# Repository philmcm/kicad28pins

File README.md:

Adaptation of 28-PINS PROJECT by FEDEVEL ACADEMY to KiCad
http://www.28pins.com

Adaptation by Phil McMillan, September 2018

(c) 2015 Designed by FEDEVEL Academy http://www.fedevel.com/academy. Based on Arduino: http://www.arduino.cc. Released under Creative Commons Attribution-ShareAlike 3.0 Unported.

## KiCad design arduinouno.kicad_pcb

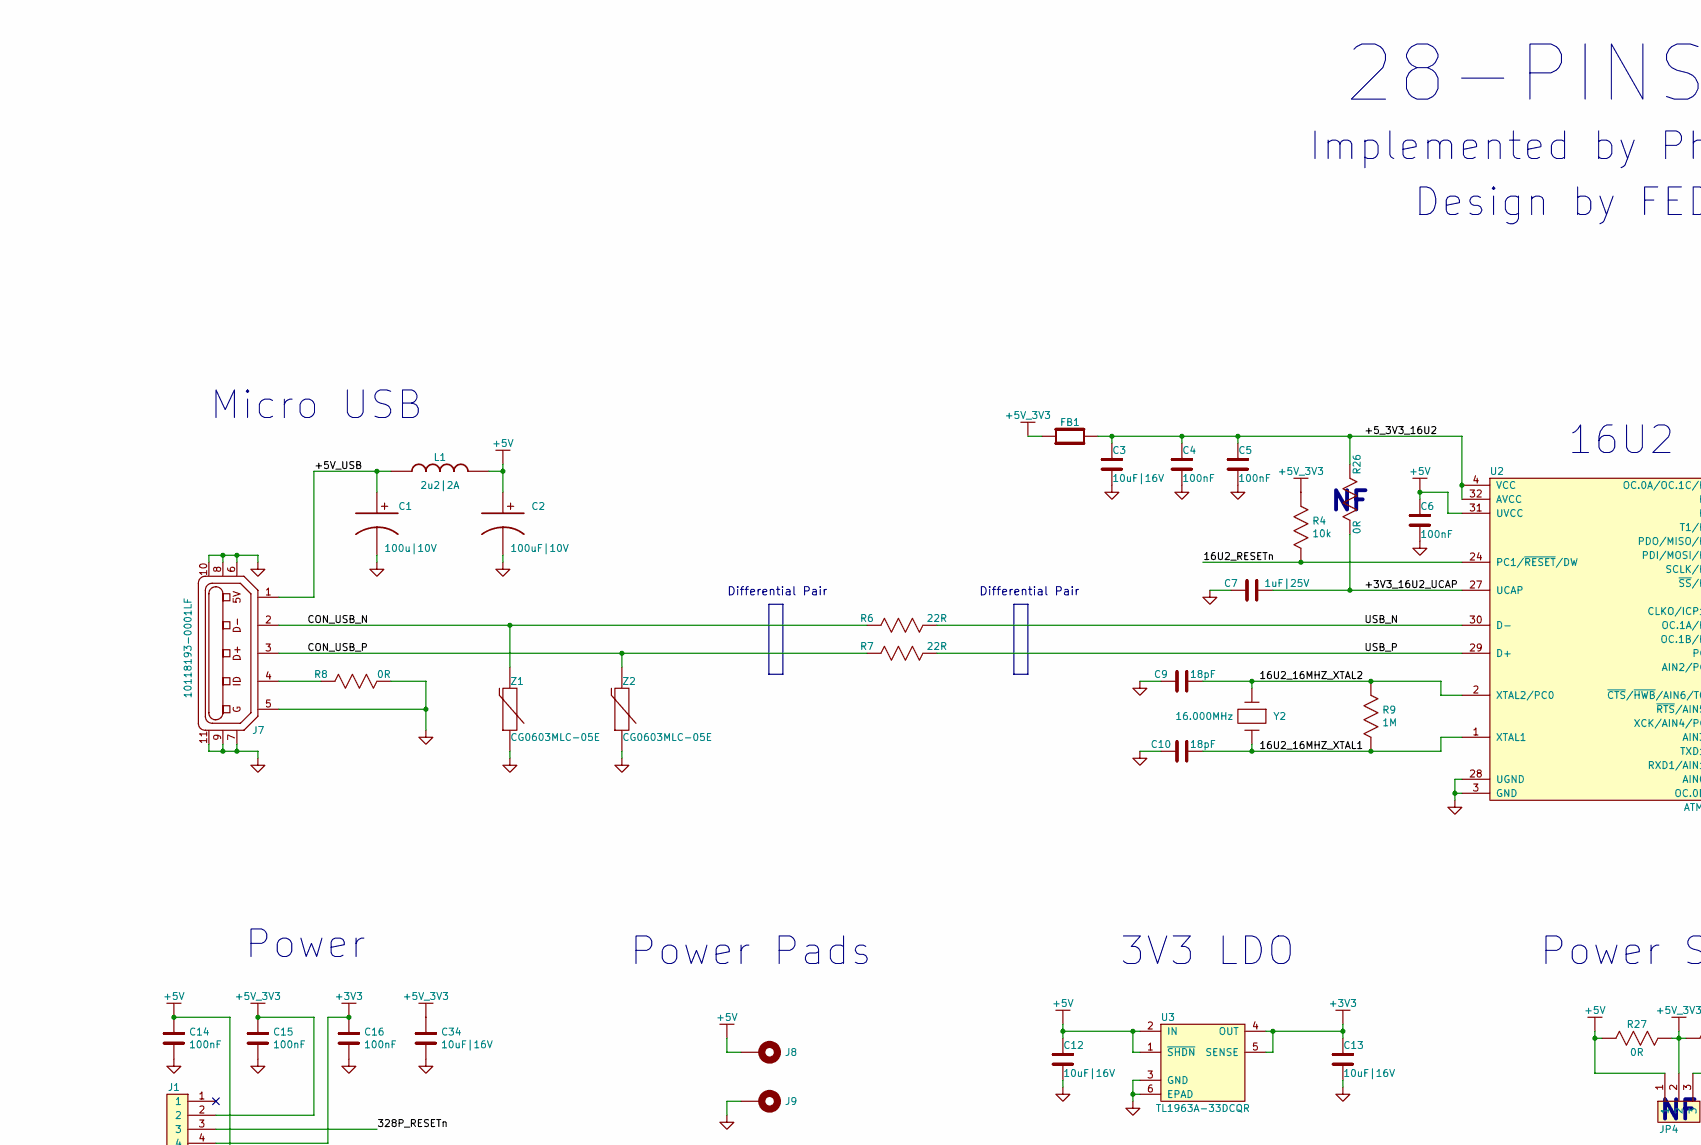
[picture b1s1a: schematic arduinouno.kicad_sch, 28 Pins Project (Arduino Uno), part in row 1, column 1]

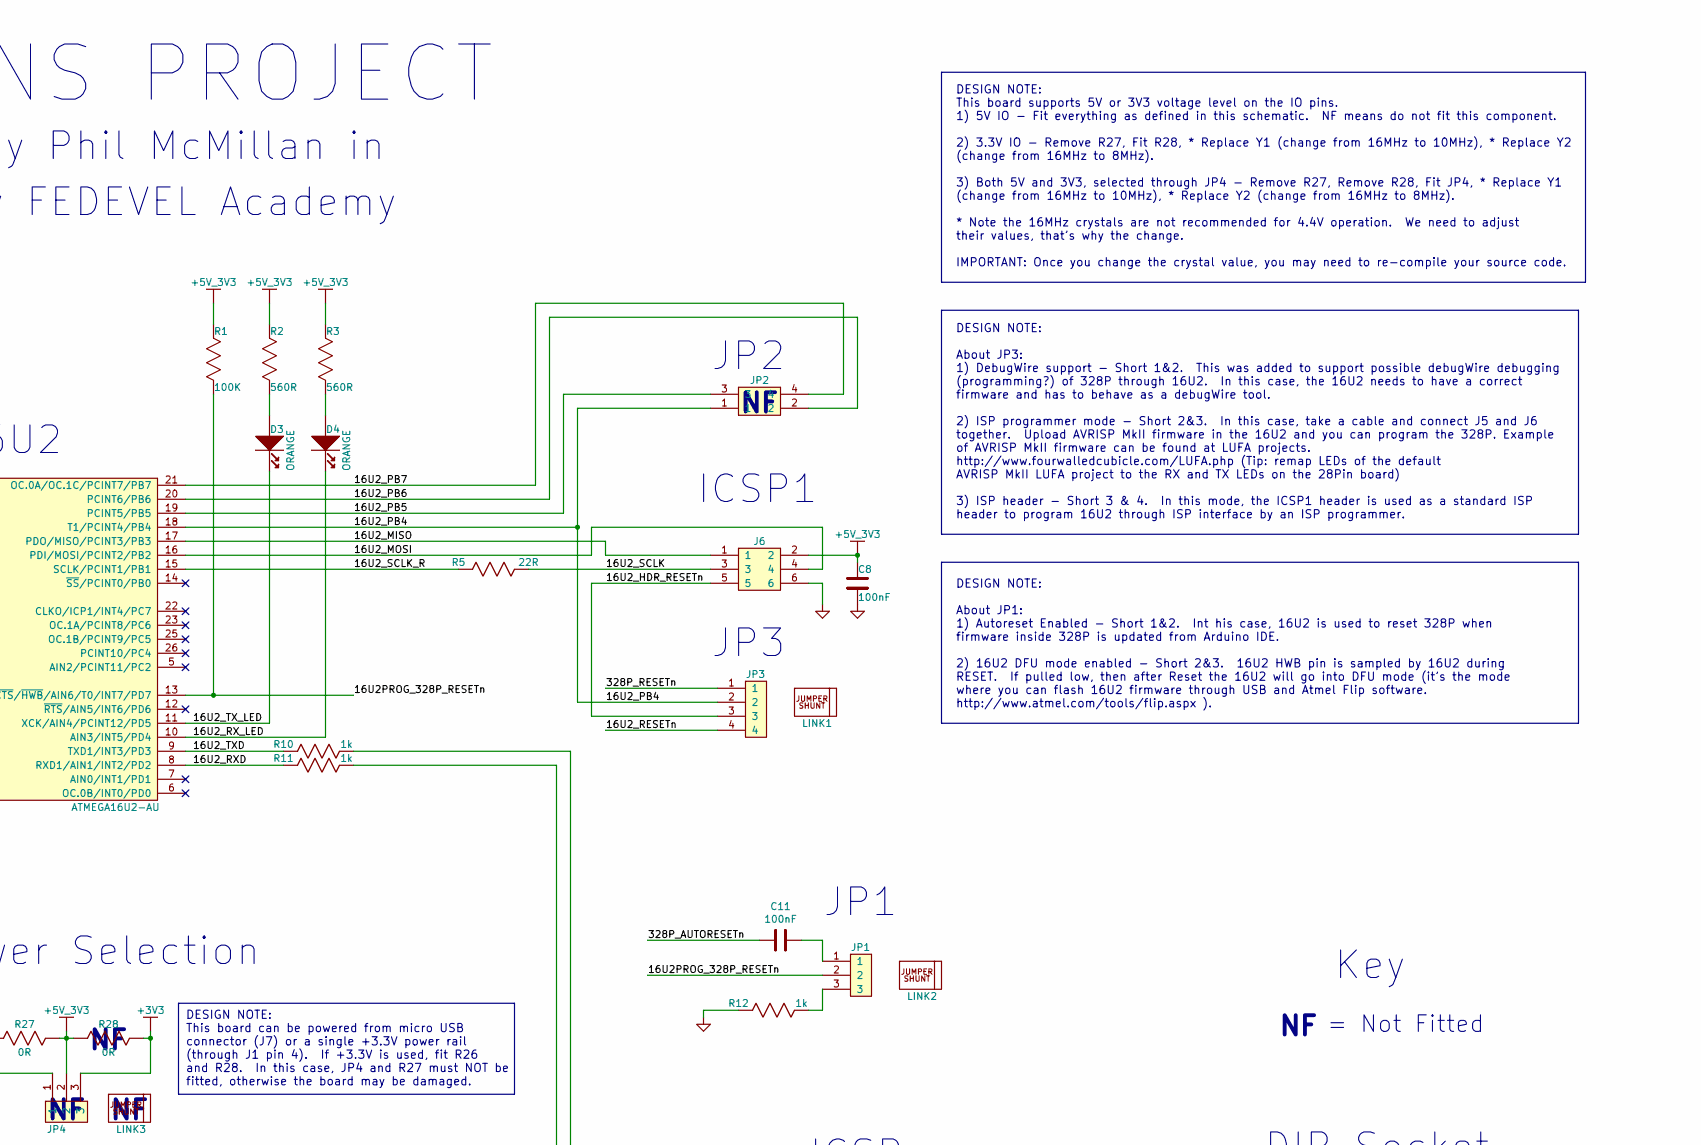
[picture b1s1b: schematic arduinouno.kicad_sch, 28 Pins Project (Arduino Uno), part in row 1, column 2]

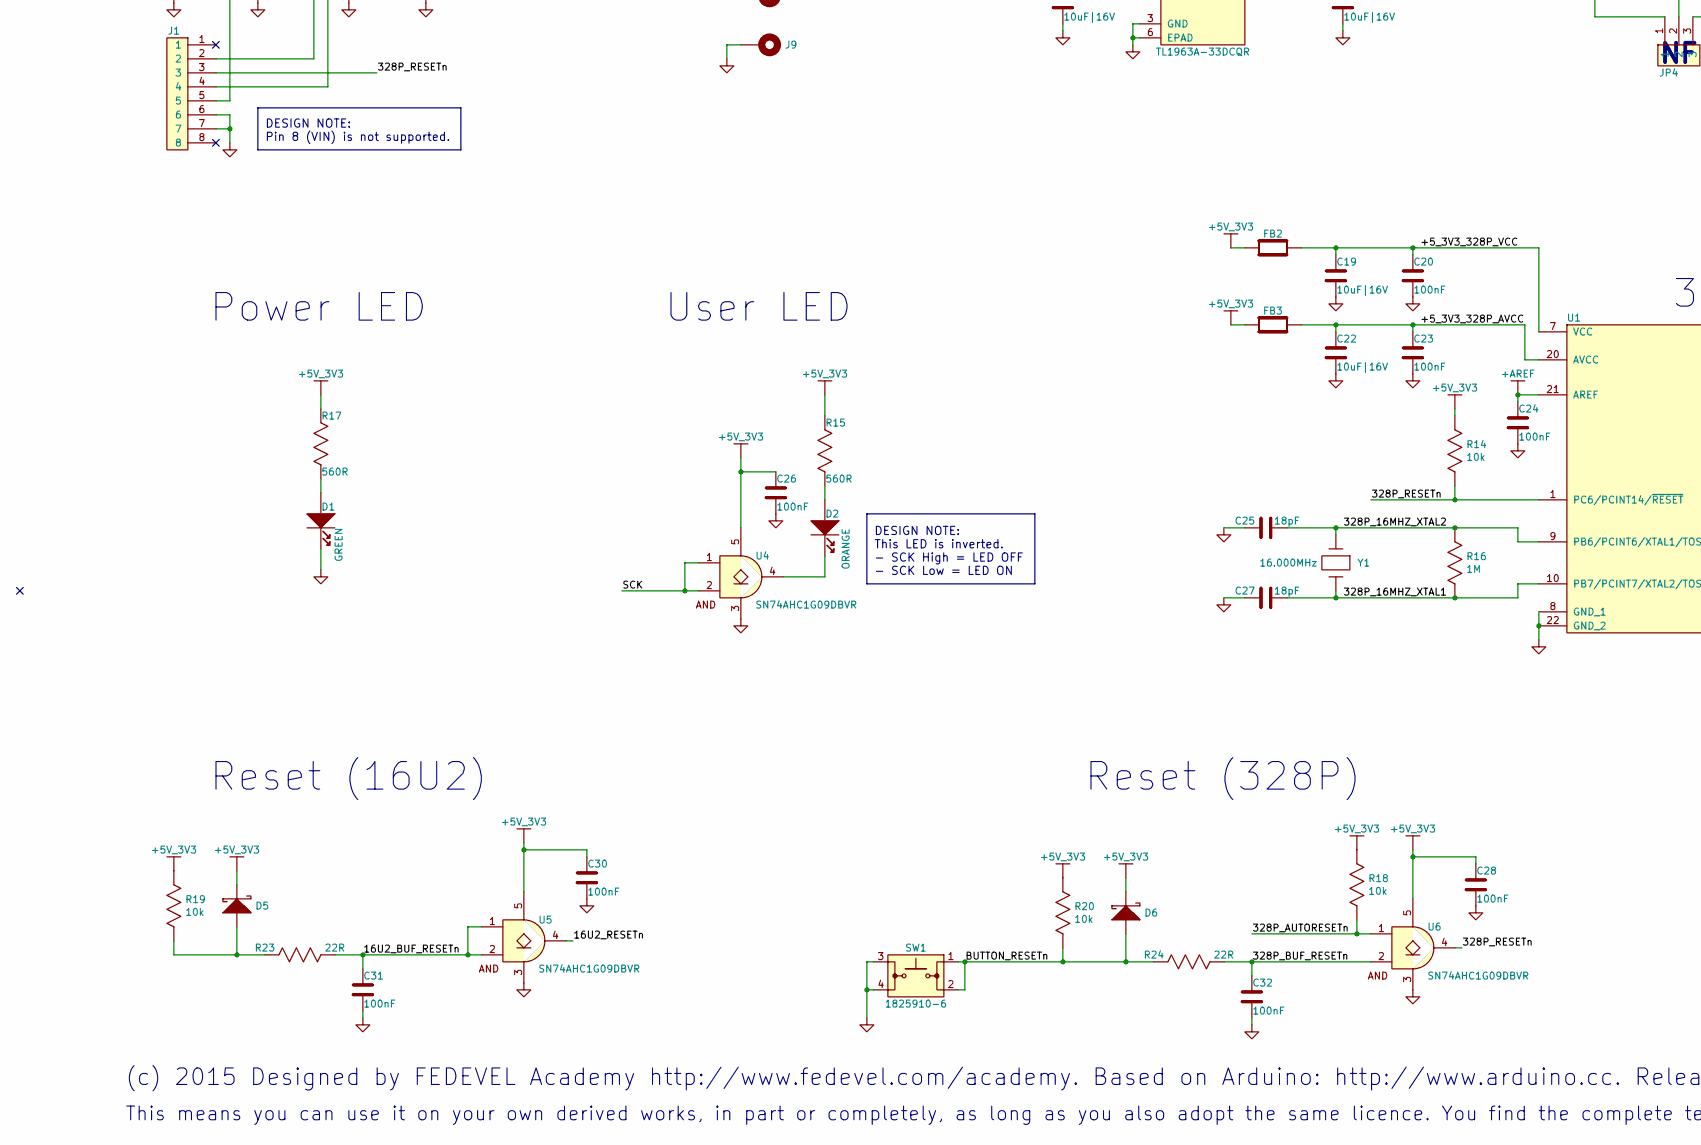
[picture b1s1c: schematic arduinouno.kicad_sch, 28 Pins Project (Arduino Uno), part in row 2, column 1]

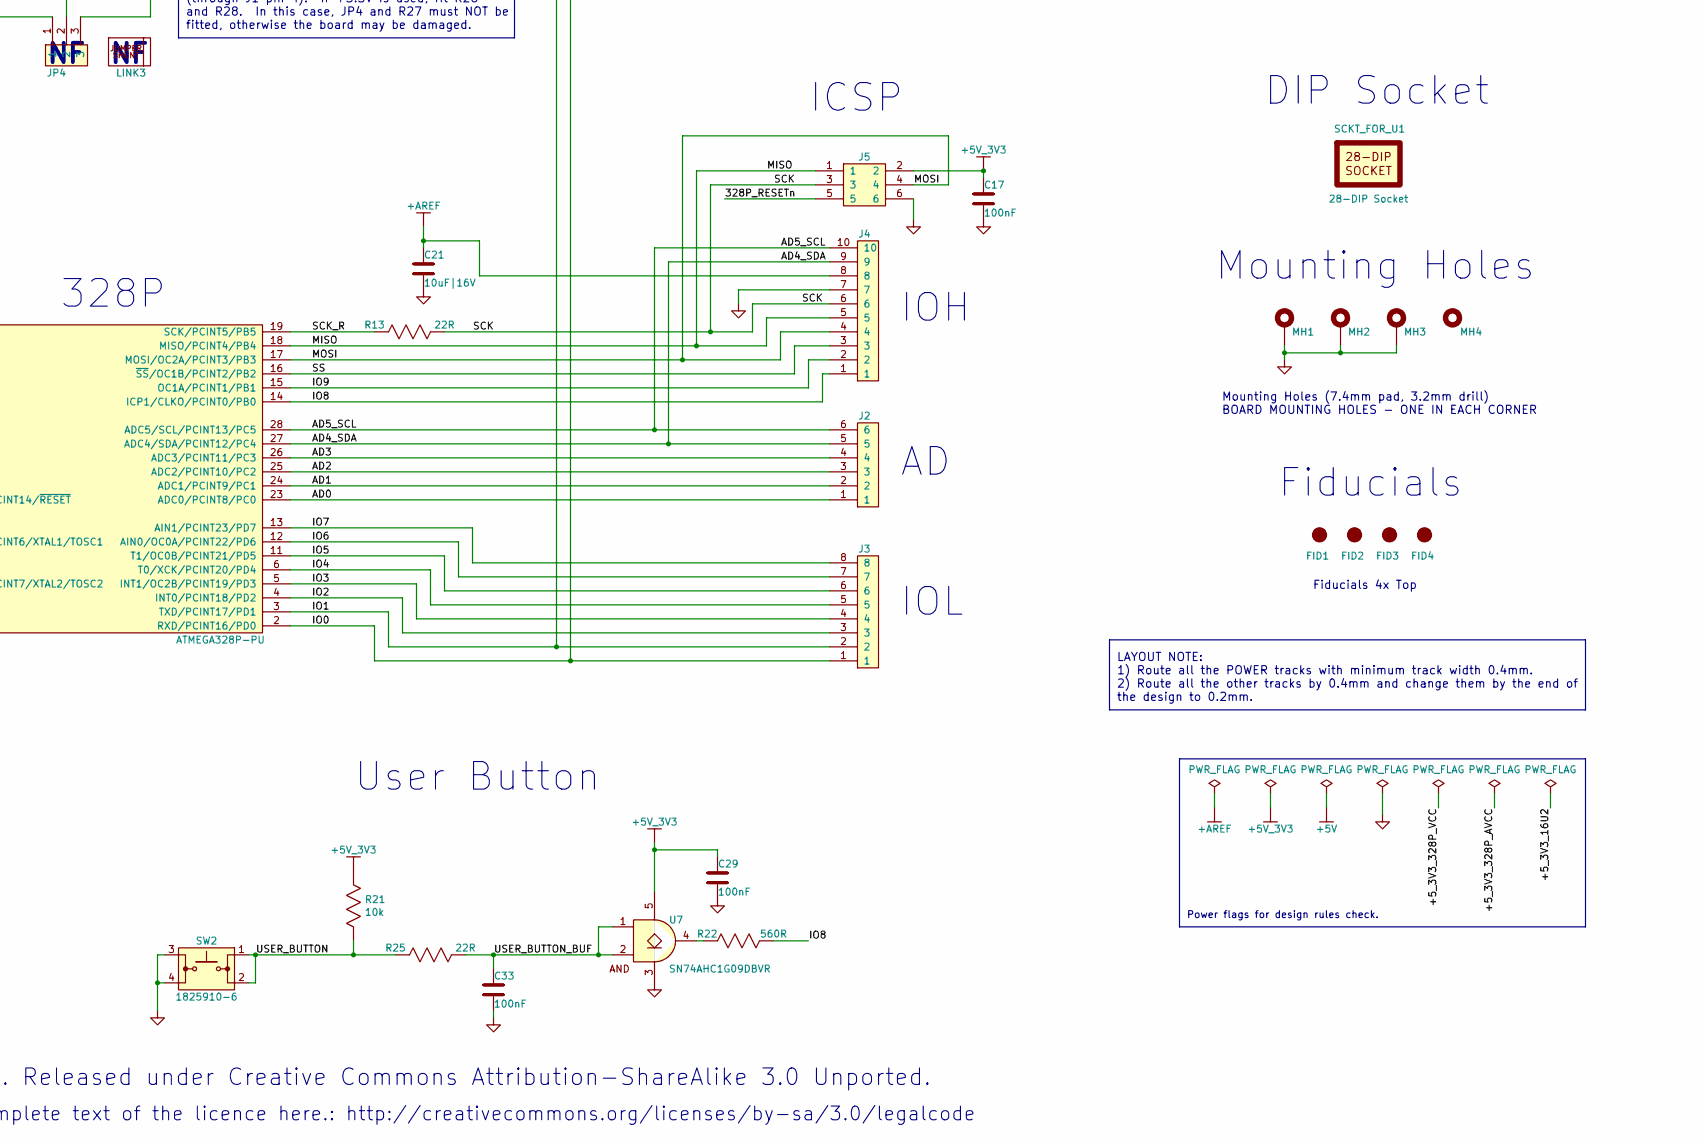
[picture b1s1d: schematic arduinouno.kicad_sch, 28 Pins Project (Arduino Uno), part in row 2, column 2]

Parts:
C1: 100u|10V; C_ALUM_C_SIZE; Digikey PCE3867TR-ND
C2: 100uF|10V; C_ALUM_C_SIZE; Digikey PCE3867TR-ND
C3, C12, C13, C19, C21, C22, C34: 10uF|16V; C0805x145mm; Digikey 445-7645-1-ND
C4, C5, C6, C8, C11, C14, C15, C16, C17, C20, C23, C24, C26, C28, C29, C30, C31, C32, C33: 100nF; C0805x95mm; Digikey 445-7534-1-ND
C7: 1uF|25V; C0805x95mm; Digikey 445-1419-1-ND
C9, C10, C25, C27: 18pF; C0805x95mm; Digikey 399-8029-1-ND
D1: GREEN; LED_0603; Digikey 475-2709-1-ND
D2, D3, D4: ORANGE; LED_0603; Digikey 475-2740-1-ND
D5, D6: BAT54HT1G; SOD323; Digikey BAT54HT1GOSTR-ND
FB1, FB2, FB3: MPZ2012S601AT000; FB0805x85mm; Digikey 445-7645-1-ND
FID1, FID2, FID3, FID4: FID_1MM; FID_40x120M
J1, J3: M20-7820842; 8P_Header_Female_2.54mm; Digikey 952-1823-ND
J2: M20-7820646; 6P_Header_Female_2.54mm; Digikey 952-1809-ND
J4: M20-7821046; 10P_Header_Female_2.54mm; Digikey 952-1847-ND
J5, J6: 67997-106HLF; HDR_2x3_2.54mm; Digikey 609-3393-ND
J7: 10118193-0001LF; 10118193; Digikey 609-4616-1-ND
J8, J9: PAD_WITH_HOLE_4mmx1.5mm
JP1, JP4: 68000-103HLF; 3P_Header_2.54mm; Digikey 609-3461-ND
JP2: 68602-104HLF; HDR_2x2_2.54mm; Digikey 609-3361-ND
JP3: 68001-204HLF; 4P_Header_2.54mm; Digikey 609-3402-ND
L1: 2u2|2A; C1210_INDUCTOR; Digikey 399-9598-1-ND
LINK1, LINK2, LINK3: QPC02SXGN-RC; Digikey S9337-ND
MH1, MH2, MH3: MH_7.4MMCx3.2MMD
MH4: MH_7.4MMNCx3.2MMD; MH_7.4MMCx3.2MMD_NON_COPPER_NPTH
R1: 100K; R0805x60mm; Digikey 311-100KCRCT-ND
R2, R3, R15, R17, R22: 560R; R0805x60mm; Digikey 311-560CRCT-ND
R4, R14, R18, R19, R20, R21: 10k; R0805x60mm; Digikey 311-10.0KCRCT-ND
R5, R6, R7, R13, R23, R24, R25: 22R; R0805x60mm; Digikey 311-22.0CRCT-ND
R8, R26, R27, R28: 0R; R0805x60mm; Digikey 311-0.0ARCT-ND
R9, R16: 1M; R0805x60mm; Digikey 311-1.00MCRCT-ND
R10, R11, R12: 1k; R0805x60mm; Digikey 311-1.00KCRCT-ND
SCKT_FOR_U1: 28-DIP Socket; 28DIP_7.62MM_SCKT; Digikey 3M5480-ND
SW1, SW2: 1825910-6; Digikey 450-1650-ND
U1: ATMEGA328P-PU; 28PIN_PDIP_7.62mm; Digikey ATMEGA328P-PU-ND
U2: ATMEGA16U2-AU; QFP-32_8.4x8.4_Pitch0.8mm; Digikey ATMEGA16U2-AU-ND
U3: TL1963A-33DCQR; DCQ_R-PDSO-G6; Digikey 296-24534-1-ND
U4, U5, U6, U7: SN74AHC1G09DBVR; DBV_SOT23_5; Digikey 296-29202-1-ND
Y1, Y2: 16.000MHz; ABM7_BIG; Digikey 535-9840-1-ND
Z1, Z2: CG0603MLC-05E; R_0603; Digikey CG0603MLC-05ECT-ND

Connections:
+3V3: C13.1, C16.1, J1.4, JP4.3, R28.2, U3.4 (OUT), U3.5 (SENSE)
+5V: C2.1, C6.1, C12.1, C14.1, J1.5, J8.1, JP4.1, L1.2, R27.1, U2.31 (UVCC), U3.1 (~SHDN), U3.2 (IN)
+5V_3V3: C8.1, C15.1, C17.1, C26.1, C28.1, C29.1, C30.1, C34.1, D5.1 (Cathode), D6.1 (Cathode), FB1.1, FB2.1, FB3.1, J1.2, J5.2, J6.2, JP4.2, R1.1, R2.1, R3.1, R4.1, R14.1, R15.1, R17.1, R18.1, R19.1, R20.1, R21.1, R27.2, R28.1, U4.5 (VCC), U5.5 (VCC), U6.5 (VCC), U7.5 (VCC)
+AREF: C21.1, C24.1, J4.8, U1.21 (AREF)
/16U2PROG_328P_RESETn: JP1.2, R1.2, U2.13 (~CTS/~HWB/AIN6/T0/INT7/PD7)
/16U2_16MHZ_XTAL1: C10.2, R9.2, U2.1 (XTAL1), Y2.2
/16U2_16MHZ_XTAL2: C9.2, R9.1, U2.2 (XTAL2/PC0), Y2.1
/16U2_BUF_RESETn: C31.1, R23.2, U5.1 (A), U5.2 (B)
/16U2_HDR_RESETn: J6.5, JP3.3
/16U2_MISO: J6.1, U2.17 (PDO/MISO/PCINT3/PB3)
/16U2_MOSI: J6.4, U2.16 (PDI/MOSI/PCINT2/PB2)
/16U2_PB4: JP2.1, JP3.2, U2.18 (T1/PCINT4/PB4)
/16U2_PB5: JP2.3, U2.19 (PCINT5/PB5)
/16U2_PB6: JP2.2, U2.20 (PCINT6/PB6)
/16U2_PB7: JP2.4, U2.21 (OC.0A/OC.1C/PCINT7/PB7)
/16U2_RESETn: JP3.4, R4.2, U2.24 (PC1/~RESET/DW), U5.4 (Y)
/16U2_RXD: R11.1, U2.8 (RXD1/AIN1/INT2/PD2)
/16U2_RX_LED: D4.1 (Cathode), U2.10 (AIN3/INT5/PD4)
/16U2_SCLK: J6.3, R5.2
/16U2_SCLK_R: R5.1, U2.15 (SCLK/PCINT1/PB1)
/16U2_TXD: R10.1, U2.9 (TXD1/INT3/PD3)
/16U2_TX_LED: D3.1 (Cathode), U2.11 (XCK/AIN4/PCINT12/PD5)
/328P_16MHZ_XTAL1: C27.2, R16.2, U1.10 (PB7/PCINT7/XTAL2/TOSC2), Y1.2
/328P_16MHZ_XTAL2: C25.2, R16.1, U1.9 (PB6/PCINT6/XTAL1/TOSC1), Y1.1
/328P_AUTORESETn: C11.1, R18.2, U6.1 (A)
/328P_BUF_RESETn: C32.1, R24.2, U6.2 (B)
/328P_RESETn: J1.3, J5.5, JP3.1, R14.2, U1.1 (PC6/PCINT14/~RESET), U6.4 (Y)
/+3V3_16U2_UCAP: C7.2, R26.2, U2.27 (UCAP)
/+5V_USB: C1.1, J7.1, L1.1
/+5_3V3_16U2: C3.1, C4.1, C5.1, FB1.2, R26.1, U2.4 (VCC), U2.32 (AVCC)
/+5_3V3_328P_AVCC: C22.1, C23.1, FB3.2, U1.20 (AVCC)
/+5_3V3_328P_VCC: C19.1, C20.1, FB2.2, U1.7 (VCC)
/AD0: J2.1, U1.23 (ADC0/PCINT8/PC0)
/AD1: J2.2, U1.24 (ADC1/PCINT9/PC1)
/AD2: J2.3, U1.25 (ADC2/PCINT10/PC2)
/AD3: J2.4, U1.26 (ADC3/PCINT11/PC3)
/AD4_SDA: J2.5, J4.9, U1.27 (ADC4/SDA/PCINT12/PC4)
/AD5_SCL: J2.6, J4.10, U1.28 (ADC5/SCL/PCINT13/PC5)
/BUTTON_RESETn: D6.2 (Anode), R20.2, R24.1, SW1.1, SW1.2
/CON_USB_N: J7.2, R6.1, Z1.2
/CON_USB_P: J7.3, R7.1, Z2.2
/IO0: J3.1, R10.2, U1.2 (RXD/PCINT16/PD0)
/IO1: J3.2, R11.2, U1.3 (TXD/PCINT17/PD1)
/IO2: J3.3, U1.4 (INT0/PCINT18/PD2)
/IO3: J3.4, U1.5 (INT1/OC2B/PCINT19/PD3)
/IO4: J3.5, U1.6 (T0/XCK/PCINT20/PD4)
/IO5: J3.6, U1.11 (T1/OC0B/PCINT21/PD5)
/IO6: J3.7, U1.12 (AIN0/OC0A/PCINT22/PD6)
/IO7: J3.8, U1.13 (AIN1/PCINT23/PD7)
/IO8: J4.1, R22.2, U1.14 (ICP1/CLKO/PCINT0/PB0)
/IO9: J4.2, U1.15 (OC1A/PCINT1/PB1)
/MISO: J4.5, J5.1, U1.18 (MISO/PCINT4/PB4)
/MOSI: J4.4, J5.4, U1.17 (MOSI/OC2A/PCINT3/PB3)
/SCK: J4.6, J5.3, R13.2, U4.1 (A), U4.2 (B)
/SCK_R: R13.1, U1.19 (SCK/PCINT5/PB5)
/SS: J4.3, U1.16 (~SS/OC1B/PCINT2/PB2)
/USB_N: R6.2, U2.30 (D-)
/USB_P: R7.2, U2.29 (D+)
/USER_BUTTON: R21.2, R25.1, SW2.1, SW2.2
/USER_BUTTON_BUF: C33.1, R25.2, U7.1 (A), U7.2 (B)
GND: C1.2, C2.2, C3.2, C4.2, C5.2, C6.2, C7.1, C8.2, C9.1, C10.1, C12.2, C13.2, C14.2, C15.2, C16.2, C17.2, C19.2, C20.2, C21.2, C22.2, C23.2, C24.2, C25.1, C26.2, C27.1, C28.2, C29.2, C30.2, C31.2, C32.2, C33.2, C34.2, D1.1 (Cathode), J1.6, J1.7, J4.7, J5.6, J6.6, J7.5, J7.6, J7.7, J7.8, J7.9, J7.10, J7.11, J9.1, MH1.1, MH2.1, MH3.1, R8.2, R12.1, SW1.3, SW1.4, SW2.3, SW2.4, U1.8 (GND_1), U1.22 (GND_2), U2.3 (GND), U2.28 (UGND), U3.3 (GND), U3.6 (EPAD), U4.3 (GND), U5.3 (GND), U6.3 (GND), U7.3 (GND), Z1.1, Z2.1
unnamed: C11.2, JP1.1
unnamed: D1.2 (Anode), R17.2
unnamed: D2.1 (Cathode), U4.4 (Y)
unnamed: D2.2 (Anode), R15.2
unnamed: D3.2 (Anode), R2.2
unnamed: D4.2 (Anode), R3.2
unnamed: D5.2 (Anode), R19.2, R23.1
unnamed: J7.4, R8.1
unnamed: JP1.3, R12.2
unnamed: R22.1, U7.4 (Y)

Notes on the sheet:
Reset (328P)
This means you can use it on your own derived works, in part or completely, as long as you also adopt the same licence. You find the complete text of the licence here.: http://creativecommons.org/licenses/by-sa/3.0/legalcode
Power Pads
Fiducials
Key
Power Selection
16U2
(c) 2015 Designed by FEDEVEL Academy http://www.fedevel.com/academy. Based on Arduino: http://www.arduino.cc. Released under Creative Commons Attribution-ShareAlike 3.0 Unported.
28-PINS PROJECT
IOH
Implemented by Phil McMillan in
User Button
DESIGN NOTE: This board supports 5V or 3V3 voltage level on the IO pins. 1) 5V IO - Fit everything as defined in this schematic. NF means do not fit this component. 2) 3.3V IO - Remove R27, Fit R28, * Replace Y1 (change from 16MHz to 10MHz), * Replace Y2 (change from 16MHz to 8MHz). 3) Both 5V and 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
Mounting Holes
Power LED
ICSP
Reset (16U2)
DESIGN NOTE: This LED is inverted. - SCK High = LED OFF - SCK Low = LED ON
Differential Pair
IOL
Design by FEDEVEL Academy
ICSP1
Power flags for design rules check.
328P
JP3
DESIGN NOTE: About JP1: 1) Autoreset Enabled - Short 1&2. Int his case, 16U2 is used to reset 328P when firmware inside 328P is updated from Arduino IDE. 2) 16U2 DFU mode enabled - Short 2&3. 16U2 HWB pin is sampled by 16U2 during RESET. If pulled low, then after Reset the 16U2 will go into DFU mod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
DESIGN NOTE: This board can be powered from micro USB connector (J7) or a single +3.3V power rail (through J1 pin 4). If +3.3V is used, fit R26 and R28. In this case, JP4 and R27 must NOT be fitted, otherwise the board may be damaged.
DIP Socket
User LED
DESIGN NOTE: Pin 8 (VIN) is not supported.
Mounting Holes (7.4mm pad, 3.2mm drill) BOARD MOUNTING HOLES - ONE IN EACH CORNER
LAYOUT NOTE: 1) Route all the POWER tracks with minimum track width 0.4mm. 2) Route all the other tracks by 0.4mm and change them by the end of the design to 0.2mm.
Fiducials 4x Top
DESIGN NOTE: About JP3: 1) DebugWire support - Short 1&2. This was added to support possible debugWire debugging (programming?) of 328P through 16U2. In this case, the 16U2 needs to have a correct firmware and has to behave as a debugWire tool. 2) ISP programmer mode - Short 2&3. In this case, take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
JP1
Power
3V3 LDO
JP2
= Not Fitted
Micro USB

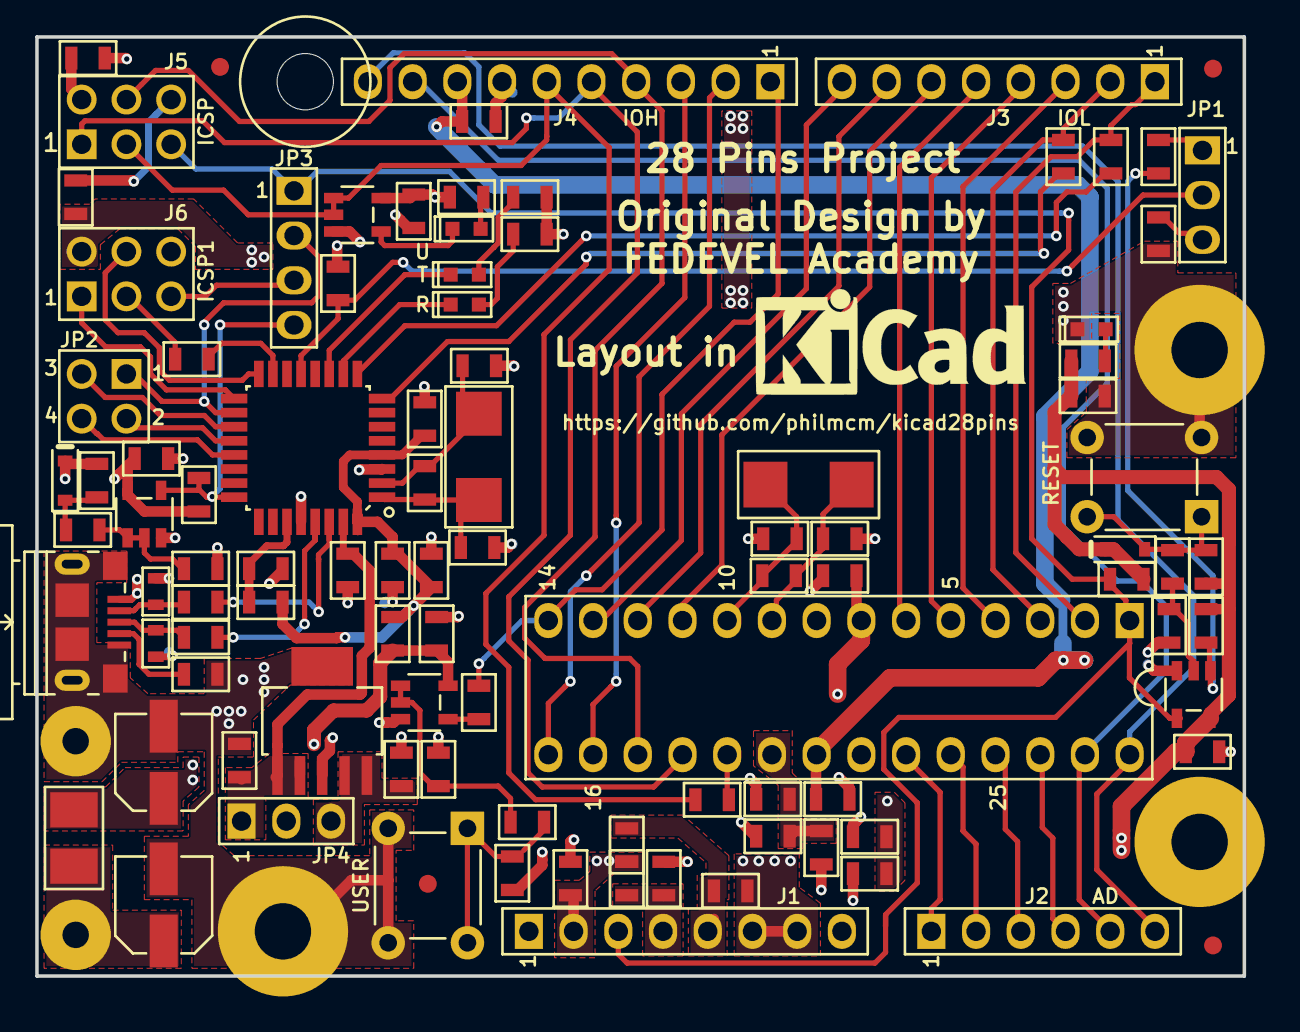
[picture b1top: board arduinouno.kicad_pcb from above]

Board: 2 copper layers, 68.6 x 53.3 mm, 106 parts (0 on the bottom side), 71 nets.

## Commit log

2018-09-15 Schematic and README updates
2018-09-16 Completed schematic capture
2018-09-16 Added schematic pdf, updated missing R26
2018-09-17 started placement; updated 3d model offsets for PDIP components
2018-09-18 finished placement
2018-09-19 updated design rules and net classes
2018-09-19 changed text height to 32mil
2018-09-20 layout continuing
2018-09-23 routed power nets 5V, 3V3, 5/3V3
2018-09-23 updated ground vias
2018-09-23 power polys done, before ground poly
2018-09-23 after ground poly
2018-09-24 improved layout, almost complete
2018-09-24 completed layout, drc ok
2018-09-25 updated silkscreen
2018-09-25 added gerbers
2018-09-25 fixed errors on silkscreen
2018-09-25 added assembly drawing
2018-09-25 fixed R27/R28 overlap on F.Fab layer
2018-09-25 updates to f.fab and assembly drawing
2023-04-05 Updated project and symbol library to kicad 7.0
2023-04-05 Added .gitignore
2023-04-05 Updated schematic to Kicad 7.0
2023-04-05 Updated pcb layout to Kicad 7.0

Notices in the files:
arduinouno.kicad_pcb:
(c) 2015 FEDEVEL
